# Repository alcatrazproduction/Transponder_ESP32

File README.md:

# Transponder_ESP32
Cano decoder compatible Transponder for MX and RC with Wifi setting and telemetry

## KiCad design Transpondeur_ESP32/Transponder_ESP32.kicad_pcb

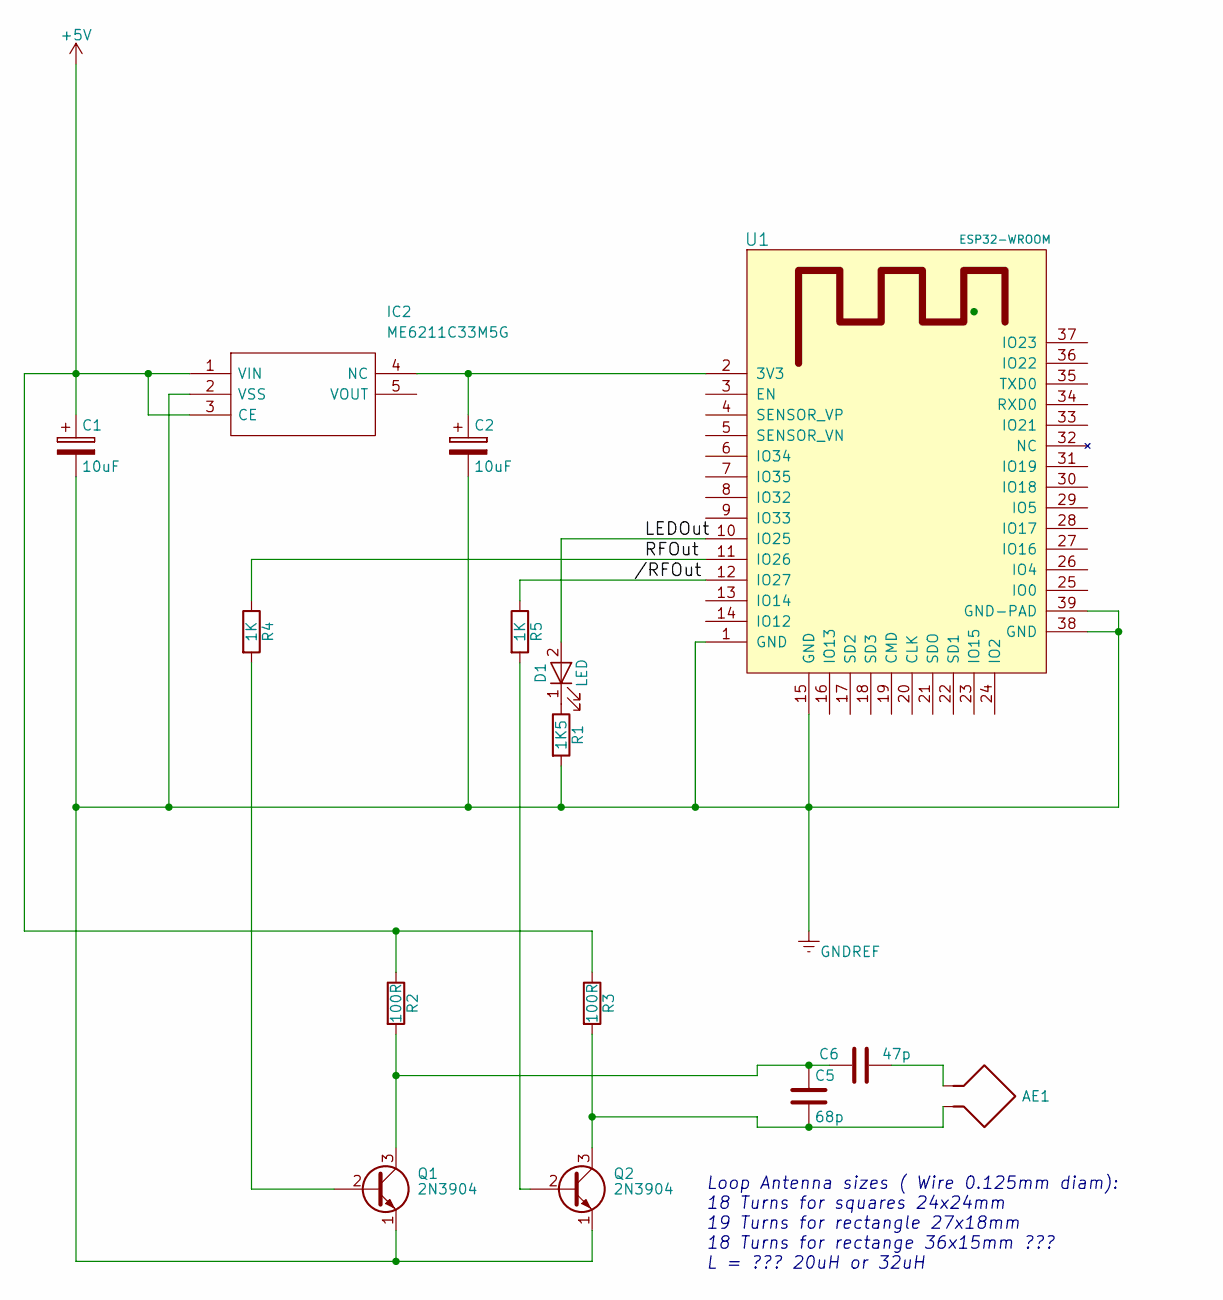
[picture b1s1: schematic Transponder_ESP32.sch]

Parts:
AE1: Loop Antenna Wire 0.125, 18turns 24x24,19 turns 2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; Socket_Strip_Angled_1x02_Pitch2.54mm
C1, C2: 10uF; C_Disc_D3.8mm_W2.6mm_P2.50mm
C5: 68p; C_Disc_D3.8mm_W2.6mm_P2.50mm
C6: 47p; C_Disc_D3.8mm_W2.6mm_P2.50mm
D1: LED; LED_D2.0mm_W4.8mm_H2.5mm_FlatTop
IC2: ME6211C33M5G; SOT95P282X145-5N; Manufacturer_Part_Number ME6211C33M5G
Q1, Q2: 2N3904; TO-92_Molded_Narrow
R1: 1K5; R_Axial_DIN0207_L6.3mm_D2.5mm_P2.54mm_Vertical
R2, R3: 100R; R_Axial_DIN0207_L6.3mm_D2.5mm_P2.54mm_Vertical
R4, R5: 1K; R_Axial_DIN0207_L6.3mm_D2.5mm_P2.54mm_Vertical
U1: ESP32-WROOM

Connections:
+5V: C1.1, IC2.1 (VIN), IC2.3 (CE), R2.1, R3.1
//RFOut: R5.1, U1.12 (IO27)
/LEDOut: D1.2 (A), U1.10 (IO25)
/RFOut: R4.1, U1.11 (IO26)
GNDREF: C1.2, C2.2, IC2.2 (VSS), Q1.1 (E), Q2.1 (E), R1.2, U1.1 (GND), U1.15 (GND), U1.38 (GND), U1.39 (GND-PAD)
unnamed: AE1.1, C6.2
unnamed: AE1.2, C5.2, Q2.3 (C), R3.2
unnamed: C2.1, IC2.4 (NC), U1.2 (3V3)
unnamed: C5.1, C6.1, Q1.3 (C), R2.2
unnamed: D1.1 (K), R1.1
unnamed: Q1.2 (B), R4.2
unnamed: Q2.2 (B), R5.2

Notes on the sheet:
Loop Antenna sizes ( Wire 0.125mm diam): 18 Turns for squares 24x24mm 19 Turns for rectangle 27x18mm 18 Turns for rectange 36x15mm ??? L = ??? 20uH or 32uH

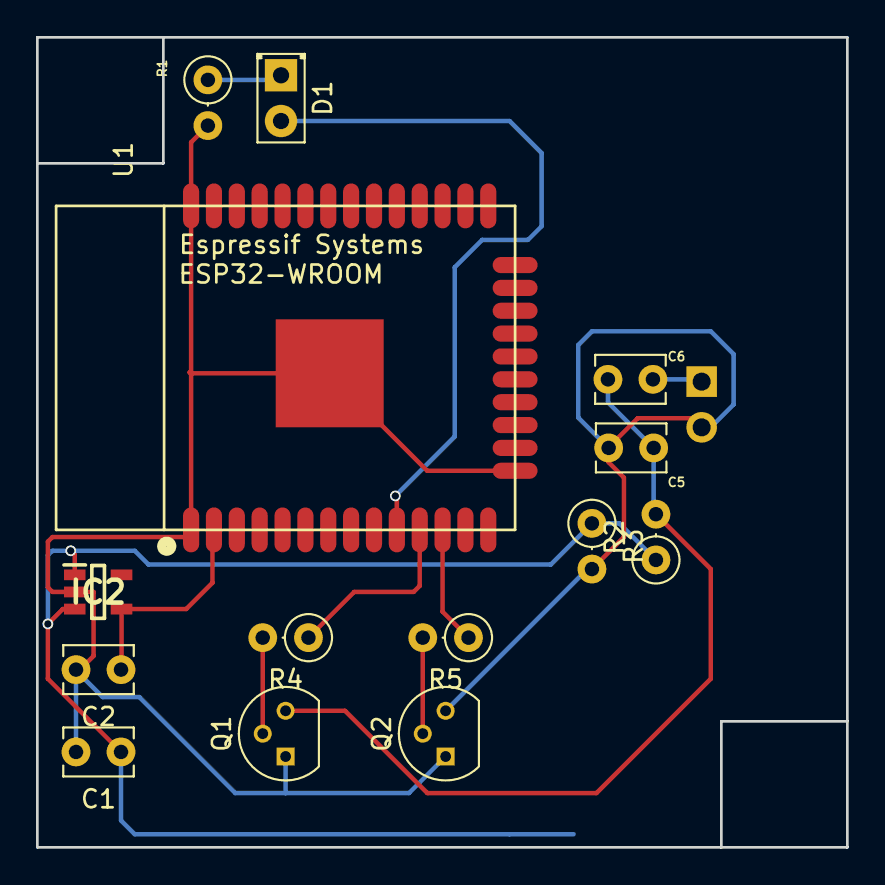
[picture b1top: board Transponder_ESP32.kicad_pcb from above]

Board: 2 copper layers, 45.0 x 45.0 mm, 15 parts (1 on the bottom side), 12 nets.
